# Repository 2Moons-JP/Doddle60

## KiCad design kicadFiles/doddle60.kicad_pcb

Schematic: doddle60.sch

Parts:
CB1, CB4, CB6: 1µ; C_0402_1005Metric
CB2, CB3, CB5, CB8: 100n; C_0402_1005Metric
CB7: 100nF; C_0402_1005Metric
CB9, CB10: 1µ; C_0805_2012Metric
CRST1: 10u; C_0805_2012Metric_Pad1.15x1.40mm_HandSolder
CRST2: 4.7n; C_0805_2012Metric_Pad1.15x1.40mm_HandSolder
CSH1, CSH2: 4.7nF; C_0805_2012Metric
CSI1: 1µ; C_0805_2012Metric_Pad1.15x1.40mm_HandSolder
CSO1: 1µ; C_0805_2012Metric_Pad1.15x1.40mm_HandSolder
CUSB1: 100n; C_0805_2012Metric_Pad1.15x1.40mm_HandSolder
D1, D2, D3, D4, D5, D6, D7, D8, D9, D10, D11, D12, D13, D14, D15, D16, D17, D18, D19, D20, D21, D22, D23, D24, D25, D26, D27, D28, D29, D30, D31, D32, D33, D34, D35, D36, D37, D38, D39, D40, D41, D42, D43, D44, D45, D46, D47, D48, D49, D50, D51, D52, D53, D54, D55, D56, D57, D58, D59, D60, D61, D62, D63, D64, D65, D66, D67, D68: 1N4148; D_SOD-123
DF1: SMF9.0CA; D_SOD-123_Bidirectional
DL1: 19-217/R6C-AL1M2VY/3T; LED_0603_1608Metric
DRST1: B0520LW; D_SOD-123
DS1: RB060M-60TR; D_SOD-123
DSH1: RB060M-60TR; D_SOD-123
F1: 1A trip PTC; Fuse_1812_4532
G1: Doddle60Logo; doddle60Logo
G2: OSHLogo; osh-logo
G3: Acheron Logo; acheronLong
G4: Doddle60Label; doddle60Label
G5: LabelMask; doddle60LabelMask
H1, H6: Half Side Hole; halfSideHole
H2: Mounting Hole; MoutingHole_Oval_7mm_5.0x2.5mm
H3, H4, H5, H7, H8, H9, H10: Oval Mounting Hole; MoutingHole_Oval_7mm_5.0x2.5mm
J1: TYPE-C-31-M12_13; TYPE-C-31-M-12
J2: Conn_01x14; PinHeader_1x14_P2.54mm_Vertical
J3: Conn_ARM_JTAG_SWD_10
L1: ACM2012-900-2P-T002; ACM2012-2P
L2: MGFL1608F1R0MT-LF; L_0603_1608Metric
L3: CMI322513U1R0KT; L_1210_3225Metric
QRST1: DTC123J; SOT-23
RCC1, RCC2: 5.1k; R_SMD_1026
RL1: 620R; R_SMD_1026
RPU1: 1.5k; R_SMD_1026
RRST1: 100k; R_SMD_1026
RSH1, RSH2: 1M; R_SMD_1026
RSI1: 100k; R_SMD_1026
RSO1: 100k; R_SMD_1026
RVDD1: R010 1%; R_SMD_1026
SW1: ESC; MX100
SW2: 1; MX100
SW3: 2; MX100
SW4: 3; MX100
SW5: 4; MX100
SW6: 5; MX100
SW7: 6; MX100
SW8: 7; MX100
SW9: 8; MX100
SW10: 9; MX100
SW11: 0; MX100
SW12: -_; MX100
SW13: +=; MX100
SW14: 2U BKSP; MX200
SW15: TAB_150; MX150
SW16: Q; MX100
SW17: W; MX100
SW18: E; MX100
SW19: R; MX100
SW20: T; MX100
SW21: Y; MX100
SW22: U; MX100
SW23: I; MX100
SW24: O; MX100
SW25: P; MX100
SW26: [{; MX100
SW27: ]}; MX100
SW28: 1U_RBKSP; MX100
SW29: CAPS_175; MX175
SW30: A; MX100
SW31: S; MX100
SW32: D; MX100
SW33: F; MX100
SW34: G; MX100
SW35: H; MX100
SW36: J; MX100
SW37: K; MX100
SW38: L; MX100
SW39: :;; MX100
SW40: @'; MX100
SW41: ~~#; MX100
SW42: LSHIFT_125; MX125
SW43: |\\; MX100
SW44: Z; MX100
SW45: X; MX100
SW46: C; MX100
SW47: V; MX100
SW48: B; MX100
SW49: N; MX100
SW50: M; MX100
SW51: <,; MX100
SW52: >.; MX100
SW53: ?/; MX100
SW54: LCTRL_125; MX125
SW55: LGUI_125; MX125
SW56, SW62: LALT_125; MX125
SW57: SPACE_275; MX275R
SW58, SW68, SW82, SW83: RALT_125; MX125
SW59: RGUI_125; MX125
SW60: RCTRL_125; MX125
SW61: LGUI_100; MX100
SW63: STEPPED_CAPS_125; MX125
SW64: 1U LBKSP; MX100
SW65: ISO_Enter; MX_ISOEnter_Vertical
SW67: MUHENKAN_100; MX100
SW70: SPACE_450; MX100
SW72: RSHIFT_275; MX275R
SW73: LSHIFT_225; MX225R
SW74: RSHIFT_175; MX175
SW75: FN_100; MX100
SW76: 150U_BKSLH; MX150
SW77: ANSI_Enter; MX225
SW78: BKSLSH_1U; MX100
SW79: RSHIFT_1.75; MX175
SW80, SW89: HENKAN_125; MX125
SW81: MUHENKAN_125; MX125
SW84: RGUI_100; MX100
SW86: KANA_100; MX100
SWRST1: SW_Push; smdPushBtn
U1: STM32F072-LQFP48; LQFP-48_7x7mm_P0.5mm
U2: USBLC6-2SC6; SOT-23-6
U3: MCP1700-3302E_SOT23; SOT-23

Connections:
3.3V: CB9.2, CSO1.2, DS1.2 (A), J3.1 (VTref), L3.1, RSO1.1, SWRST1.1, U3.2 (VO)
5V: CSI1.2, DS1.1 (K), L2.2, RL1.1, RSI1.1, U3.3 (VI)
/SHIELD: CSH1.2, J1.S (SHIELD), RSH1.1
BOOT0: CRST1.2, DRST1.1 (K), RRST1.1, U1.44 (BOOT0)
CASE: DSH1.2 (A), H8.1
Col1: SW1.1 (Col), SW15.1 (Col), SW29.1 (Col), SW42.1 (Col), SW61.1 (Col), SW63.1 (Col), SW73.1 (Col), U1.18 (PB0/TIM3_CH3/ADC_IN8)
Col2: SW2.1 (Col), SW16.1 (Col), SW30.1 (Col), SW43.1 (Col), SW54.1 (Col), SW55.1 (Col), U1.15 (PA5/ADC_IN5/DAC_OUT2)
Col3: SW3.1 (Col), SW17.1 (Col), SW31.1 (Col), SW44.1 (Col), SW56.1 (Col), SW62.1 (Col), U1.14 (PA4/TIM14_CH1/ADC_IN4)
Col4: SW4.1 (Col), SW18.1 (Col), SW32.1 (Col), SW45.1 (Col), SW67.1 (Col), SW81.1 (Col), U1.13 (PA3/TIM15_CH2/ADC_IN3)
Col5: SW5.1 (Col), SW19.1 (Col), SW33.1 (Col), SW46.1 (Col), U1.12 (PA2/ADC_IN2)
Col6: SW6.1 (Col), SW20.1 (Col), SW34.1 (Col), SW47.1 (Col), U1.11 (PA1/ADC_IN1)
Col7: SW7.1 (Col), SW21.1 (Col), SW35.1 (Col), SW48.1 (Col), SW57.1 (Col), SW70.1 (Col), U1.10 (PA0/ADC_IN0)
Col8: SW8.1 (Col), SW22.1 (Col), SW36.1 (Col), SW49.1 (Col), SW86.1 (Col), SW89.1 (Col), U1.6 (PF1/OSC_OUT)
Col9: SW9.1 (Col), SW23.1 (Col), SW37.1 (Col), SW50.1 (Col), SW80.1 (Col), U1.5 (PF0/OSC_IN)
Col10: SW10.1 (Col), SW24.1 (Col), SW38.1 (Col), SW51.1 (Col), U1.4 (PC15/OSC32_OUT)
Col11: SW11.1 (Col), SW25.1 (Col), SW39.1 (Col), SW52.1 (Col), SW68.1 (Col), SW82.1 (Col), U1.3 (PC14/OSC32_IN)
Col12: SW12.1 (Col), SW26.1 (Col), SW40.1 (Col), SW53.1 (Col), SW58.1 (Col), SW83.1 (Col), U1.2 (PC13)
Col13: SW13.1 (Col), SW27.1 (Col), SW41.1 (Col), SW59.1 (Col), SW72.1 (Col), SW74.1 (Col), SW78.1 (Col), SW84.1 (Col), U1.46 (SPI2_NSS/I2S2_WS/I2C1_SDA/TIM17_CH1/PB9)
Col14: SW14.1 (Col), SW28.1 (Col), SW60.1 (Col), SW64.1 (Col), SW65.1 (Col), SW75.1 (Col), SW77.1 (Col), SW79.1 (Col), U1.45 (I2C1_SCL/TIM16_CH1/PB8)
Col15: SW76.1 (Col), U1.41 (SPI1_MOSI/I2S1_SD/TIM3_CH2/PB5)
D+: L1.3, U1.33 (USB_DP/PA12)
D-: L1.4, U1.32 (USB_DM/TIM1_CH4/PA11)
DBus+: J1.A6 (D+), J1.B6 (D+), RPU1.2, U2.6 (IO1)
DBus-: J1.A7 (D-), J1.B7 (D-), U2.4 (IO2)
Extra1: J2.1
Extra2: J2.2, U1.40 (SPI1_MISO/I2S1_MCK/TIM3_CH1/PB4)
Extra3: J2.3, U1.39 (SPI1_SCK/I2S1_CK/TIM2_CH2/PB3)
Extra4: J2.4, U1.38 (PA2)
Extra5: J2.5, U1.31 (TIM1_CH3/PA10)
Extra6: J2.6, U1.30 (TIM1_CH2/PA9)
Extra7: J2.7, U1.29 (TIM1_CH1/PA8)
Extra8: J2.8, U1.28 (SPI2_MOSI/I2S2_SD/PB15)
Extra9: J2.9, U1.27 (PB14/SPI2_MISO/I2S2_MCK/I2C2_SDA/TIM15_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)
Extra10: J2.10, U1.26 (SPI2_SCK/I2S2_CK/I2C2_SCL/PB13)
Extra11: J2.11, U1.25 (PB12)
Extra12: J2.12, U1.22 (PB11/TIM2_CH4/I2C2_SDA)
Extra13: J2.13, U1.21 (PB10/SPI2_SCK/I2C2_SCL/TIM2_CH3)
Extra14: J2.14, U1.20 (PB2)
GND: CB9.1, CRST1.1, CRST2.2, CSH1.1, CSH2.1, CSI1.1, CSO1.1, CUSB1.1, DF1.2 (A2), DL1.1 (K), J1.A1 (GND), J1.B1 (GND), J3.3 (GND), J3.5 (GND), J3.9 (GNDDetect), QRST1.2 (E), RCC1.1, RCC2.1, RRST1.2, RSH1.2, RSH2.2, RSI1.2, RSO1.2, RVDD1.2, U2.2 (GND), U3.1 (GND)
GNDD: CB1.1, CB2.1, CB3.1, CB4.1, CB5.1, CB6.1, CB7.2, CB8.1, CB10.1, RVDD1.1, U1.8 (VSSA), U1.23 (VSS), U1.35 (VSS), U1.47 (VSS)
NRST: CRST2.1, J3.10 (~RESET~), QRST1.3 (C), U1.7 (NRST)
unnamed: CSH2.2, DSH1.1 (K), RSH2.1
unnamed: D1.2 (A), SW1.2 (Row)
unnamed: D2.2 (A), SW2.2 (Row)
unnamed: D3.2 (A), SW3.2 (Row)
unnamed: D4.2 (A), SW4.2 (Row)
unnamed: D5.2 (A), SW5.2 (Row)
unnamed: D6.2 (A), SW6.2 (Row)
unnamed: D7.2 (A), SW7.2 (Row)
unnamed: D8.2 (A), SW8.2 (Row)
unnamed: D9.2 (A), SW9.2 (Row)
unnamed: D10.2 (A), SW10.2 (Row)
unnamed: D11.2 (A), SW11.2 (Row)
unnamed: D12.2 (A), SW12.2 (Row)
unnamed: D13.2 (A), SW13.2 (Row)
unnamed: D14.2 (A), SW14.2 (Row), SW64.2 (Row)
unnamed: D15.2 (A), SW15.2 (Row)
unnamed: D16.2 (A), SW16.2 (Row)
unnamed: D17.2 (A), SW17.2 (Row)
unnamed: D18.2 (A), SW18.2 (Row)
unnamed: D19.2 (A), SW19.2 (Row)
unnamed: D20.2 (A), SW20.2 (Row)
unnamed: D21.2 (A), SW21.2 (Row)
unnamed: D22.2 (A), SW22.2 (Row)
unnamed: D23.2 (A), SW23.2 (Row)
unnamed: D24.2 (A), SW24.2 (Row)
unnamed: D25.2 (A), SW25.2 (Row)
unnamed: D26.2 (A), SW26.2 (Row)
unnamed: D27.2 (A), SW27.2 (Row)
unnamed: D28.2 (A), SW28.2 (Row)
unnamed: D29.2 (A), SW29.2 (Row), SW63.2 (Row)
unnamed: D30.2 (A), SW30.2 (Row)
unnamed: D31.2 (A), SW31.2 (Row)
unnamed: D32.2 (A), SW32.2 (Row)
unnamed: D33.2 (A), SW33.2 (Row)
unnamed: D34.2 (A), SW34.2 (Row)
unnamed: D35.2 (A), SW35.2 (Row)
unnamed: D36.2 (A), SW36.2 (Row)
unnamed: D37.2 (A), SW37.2 (Row)
unnamed: D38.2 (A), SW38.2 (Row)
unnamed: D39.2 (A), SW39.2 (Row)
unnamed: D40.2 (A), SW40.2 (Row)
unnamed: D41.2 (A), SW41.2 (Row)
unnamed: D42.2 (A), SW42.2 (Row), SW73.2 (Row)
unnamed: D43.2 (A), SW43.2 (Row)
unnamed: D44.2 (A), SW44.2 (Row)
unnamed: D45.2 (A), SW45.2 (Row)
unnamed: D46.2 (A), SW46.2 (Row)
unnamed: D47.2 (A), SW47.2 (Row)
unnamed: D48.2 (A), SW48.2 (Row)
unnamed: D49.2 (A), SW49.2 (Row)
unnamed: D50.2 (A), SW50.2 (Row)
unnamed: D51.2 (A), SW51.2 (Row)
unnamed: D52.2 (A), SW52.2 (Row)
unnamed: D53.2 (A), SW53.2 (Row)
unnamed: D54.2 (A), SW61.2 (Row)
unnamed: D55.2 (A), SW54.2 (Row), SW55.2 (Row)
unnamed: D56.2 (A), SW56.2 (Row), SW62.2 (Row)
unnamed: D57.2 (A), SW57.2 (Row), SW70.2 (Row)
unnamed: D58.2 (A), SW58.2 (Row), SW83.2 (Row)
unnamed: D59.2 (A), SW59.2 (Row), SW84.2 (Row)
unnamed: D60.2 (A), SW60.2 (Row)
unnamed: D61.2 (A), SW68.2 (Row), SW82.2 (Row)
unnamed: D62.2 (A), SW72.2 (Row), SW74.2 (Row), SW78.2 (Row)
unnamed: D63.2 (A), SW75.2 (Row), SW79.2 (Row)
unnamed: D64.2 (A), SW67.2 (Row), SW81.2 (Row)
unnamed: D65.2 (A), SW65.2 (Row), SW77.2 (Row)
unnamed: D66.2 (A), SW86.2 (Row), SW89.2 (Row)
unnamed: D67.2 (A), SW80.2 (Row)
unnamed: D68.2 (A), SW76.2 (Row)
unnamed: DF1.1 (A1), F1.1, L2.1
unnamed: DL1.2 (A), RL1.2
unnamed: DRST1.2 (A), QRST1.1 (B), SWRST1.2
unnamed: J1.A5 (CC1), RCC2.2
unnamed: J1.B5 (CC2), RCC1.2
unnamed: L1.1, U2.3 (IO2)
unnamed: L1.2, U2.1 (IO1)
Row1: D1.1 (K), D2.1 (K), D3.1 (K), D4.1 (K), D5.1 (K), D6.1 (K), D7.1 (K), D8.1 (K), D9.1 (K), D10.1 (K), D11.1 (K), D12.1 (K), D13.1 (K), D14.1 (K), U1.43 (2C1_SDA/PB7)
Row2: D15.1 (K), D16.1 (K), D17.1 (K), D18.1 (K), D19.1 (K), D20.1 (K), D21.1 (K), D22.1 (K), D23.1 (K), D24.1 (K), D25.1 (K), D26.1 (K), D27.1 (K), D28.1 (K), D68.1 (K), U1.42 (I2C1_SCL/PB6)
Row3: D29.1 (K), D30.1 (K), D31.1 (K), D32.1 (K), D33.1 (K), D34.1 (K), D35.1 (K), D36.1 (K), D37.1 (K), D38.1 (K), D39.1 (K), D40.1 (K), D41.1 (K), D65.1 (K), U1.16 (PA6/ADC_IN6/TIM3_CH1/TIM16_CH1)
Row4: D42.1 (K), D43.1 (K), D44.1 (K), D45.1 (K), D46.1 (K), D47.1 (K), D48.1 (K), D49.1 (K), D50.1 (K), D51.1 (K), D52.1 (K), D53.1 (K), D62.1 (K), D63.1 (K), U1.17 (PA7/TIM3_CH2/TIM14_CH1/ADC_IN7)
Row5: D54.1 (K), D55.1 (K), D56.1 (K), D57.1 (K), D58.1 (K), D59.1 (K), D60.1 (K), D61.1 (K), D64.1 (K), D66.1 (K), D67.1 (K), U1.19 (PB1/TIM3_CH4/TIM14_CH1/ADC_IN9)
SWCLK: J3.4 (SWDCLK/TCK), U1.37 (SWCLK/PA14)
SWDIO: J3.2 (SWDIO/TMS), U1.34 (SWDIO/PA13)
VBUS: CUSB1.2, F1.2, J1.A4 (VBUS), J1.B4 (VBUS), RPU1.1, U2.5 (VBUS)
VDD: CB1.2, CB2.2, CB3.2, CB4.2, CB5.2, CB6.2, CB7.1, CB8.2, CB10.2, L3.2, U1.1 (VBAT), U1.9 (VDDA), U1.24 (VDD), U1.36 (VDDIO2), U1.48 (VDD)

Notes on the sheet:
Hard reset circuit
Power supply and protection circuit
Logos and flags
Serial programming
[1] STM32F072x8 / STM32F072xB datasheet
REFERENCES
https://www.st.com/resource/en/datasheet/stm32f072rb.pdf
[2] AN4080 Application note
https://www.st.com/content/ccc/resource/technical/document/application_note/c9/19/d7/b8/6b/0e/4c/d3/DM00051986.pdf/files/DM00051986.pdf/jcr:content/translations/en.DM00051986.pdf
MCU
USB Connector
Shield
USD ESD
CBx are the bypass capacitors. Their value is specified in reference [2].
Case ESD
Switch matrix
Mounting holes
Extra pins

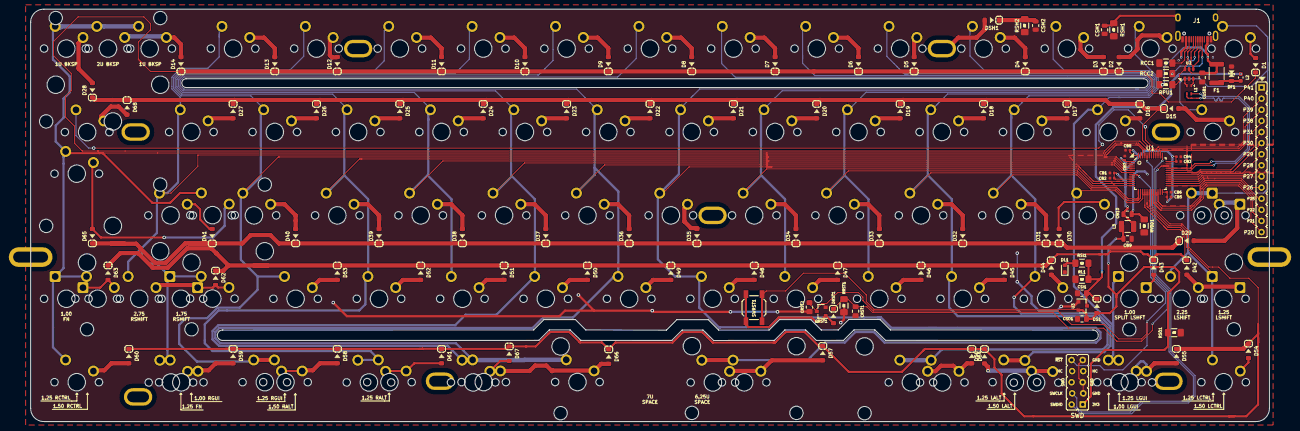
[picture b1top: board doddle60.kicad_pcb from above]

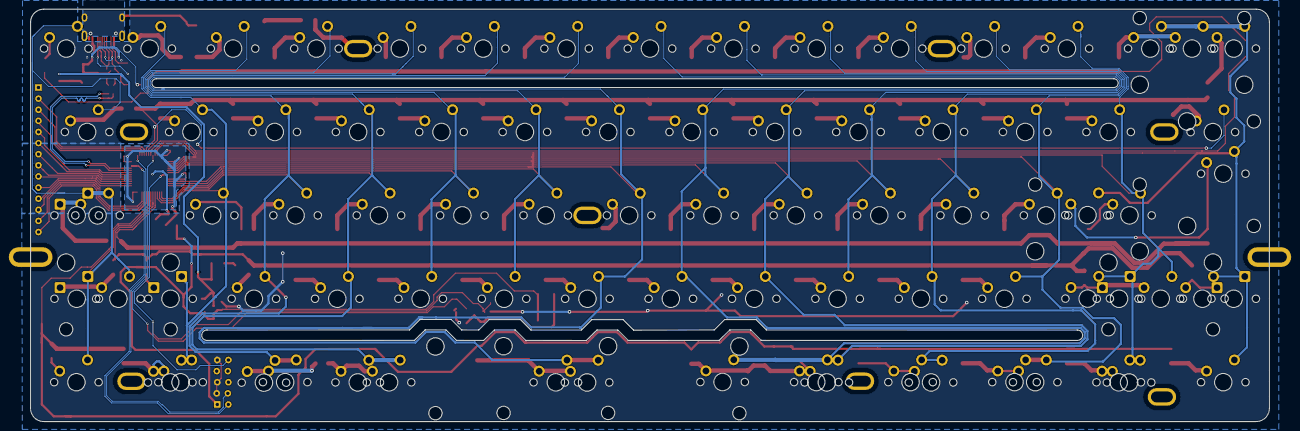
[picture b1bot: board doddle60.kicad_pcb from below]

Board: 2 copper layers, 283.0 x 94.2 mm, 210 parts (7 on the bottom side), 125 nets.

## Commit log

2020-10-18 PCB1
2021-01-24 cache
2021-01-24 library
